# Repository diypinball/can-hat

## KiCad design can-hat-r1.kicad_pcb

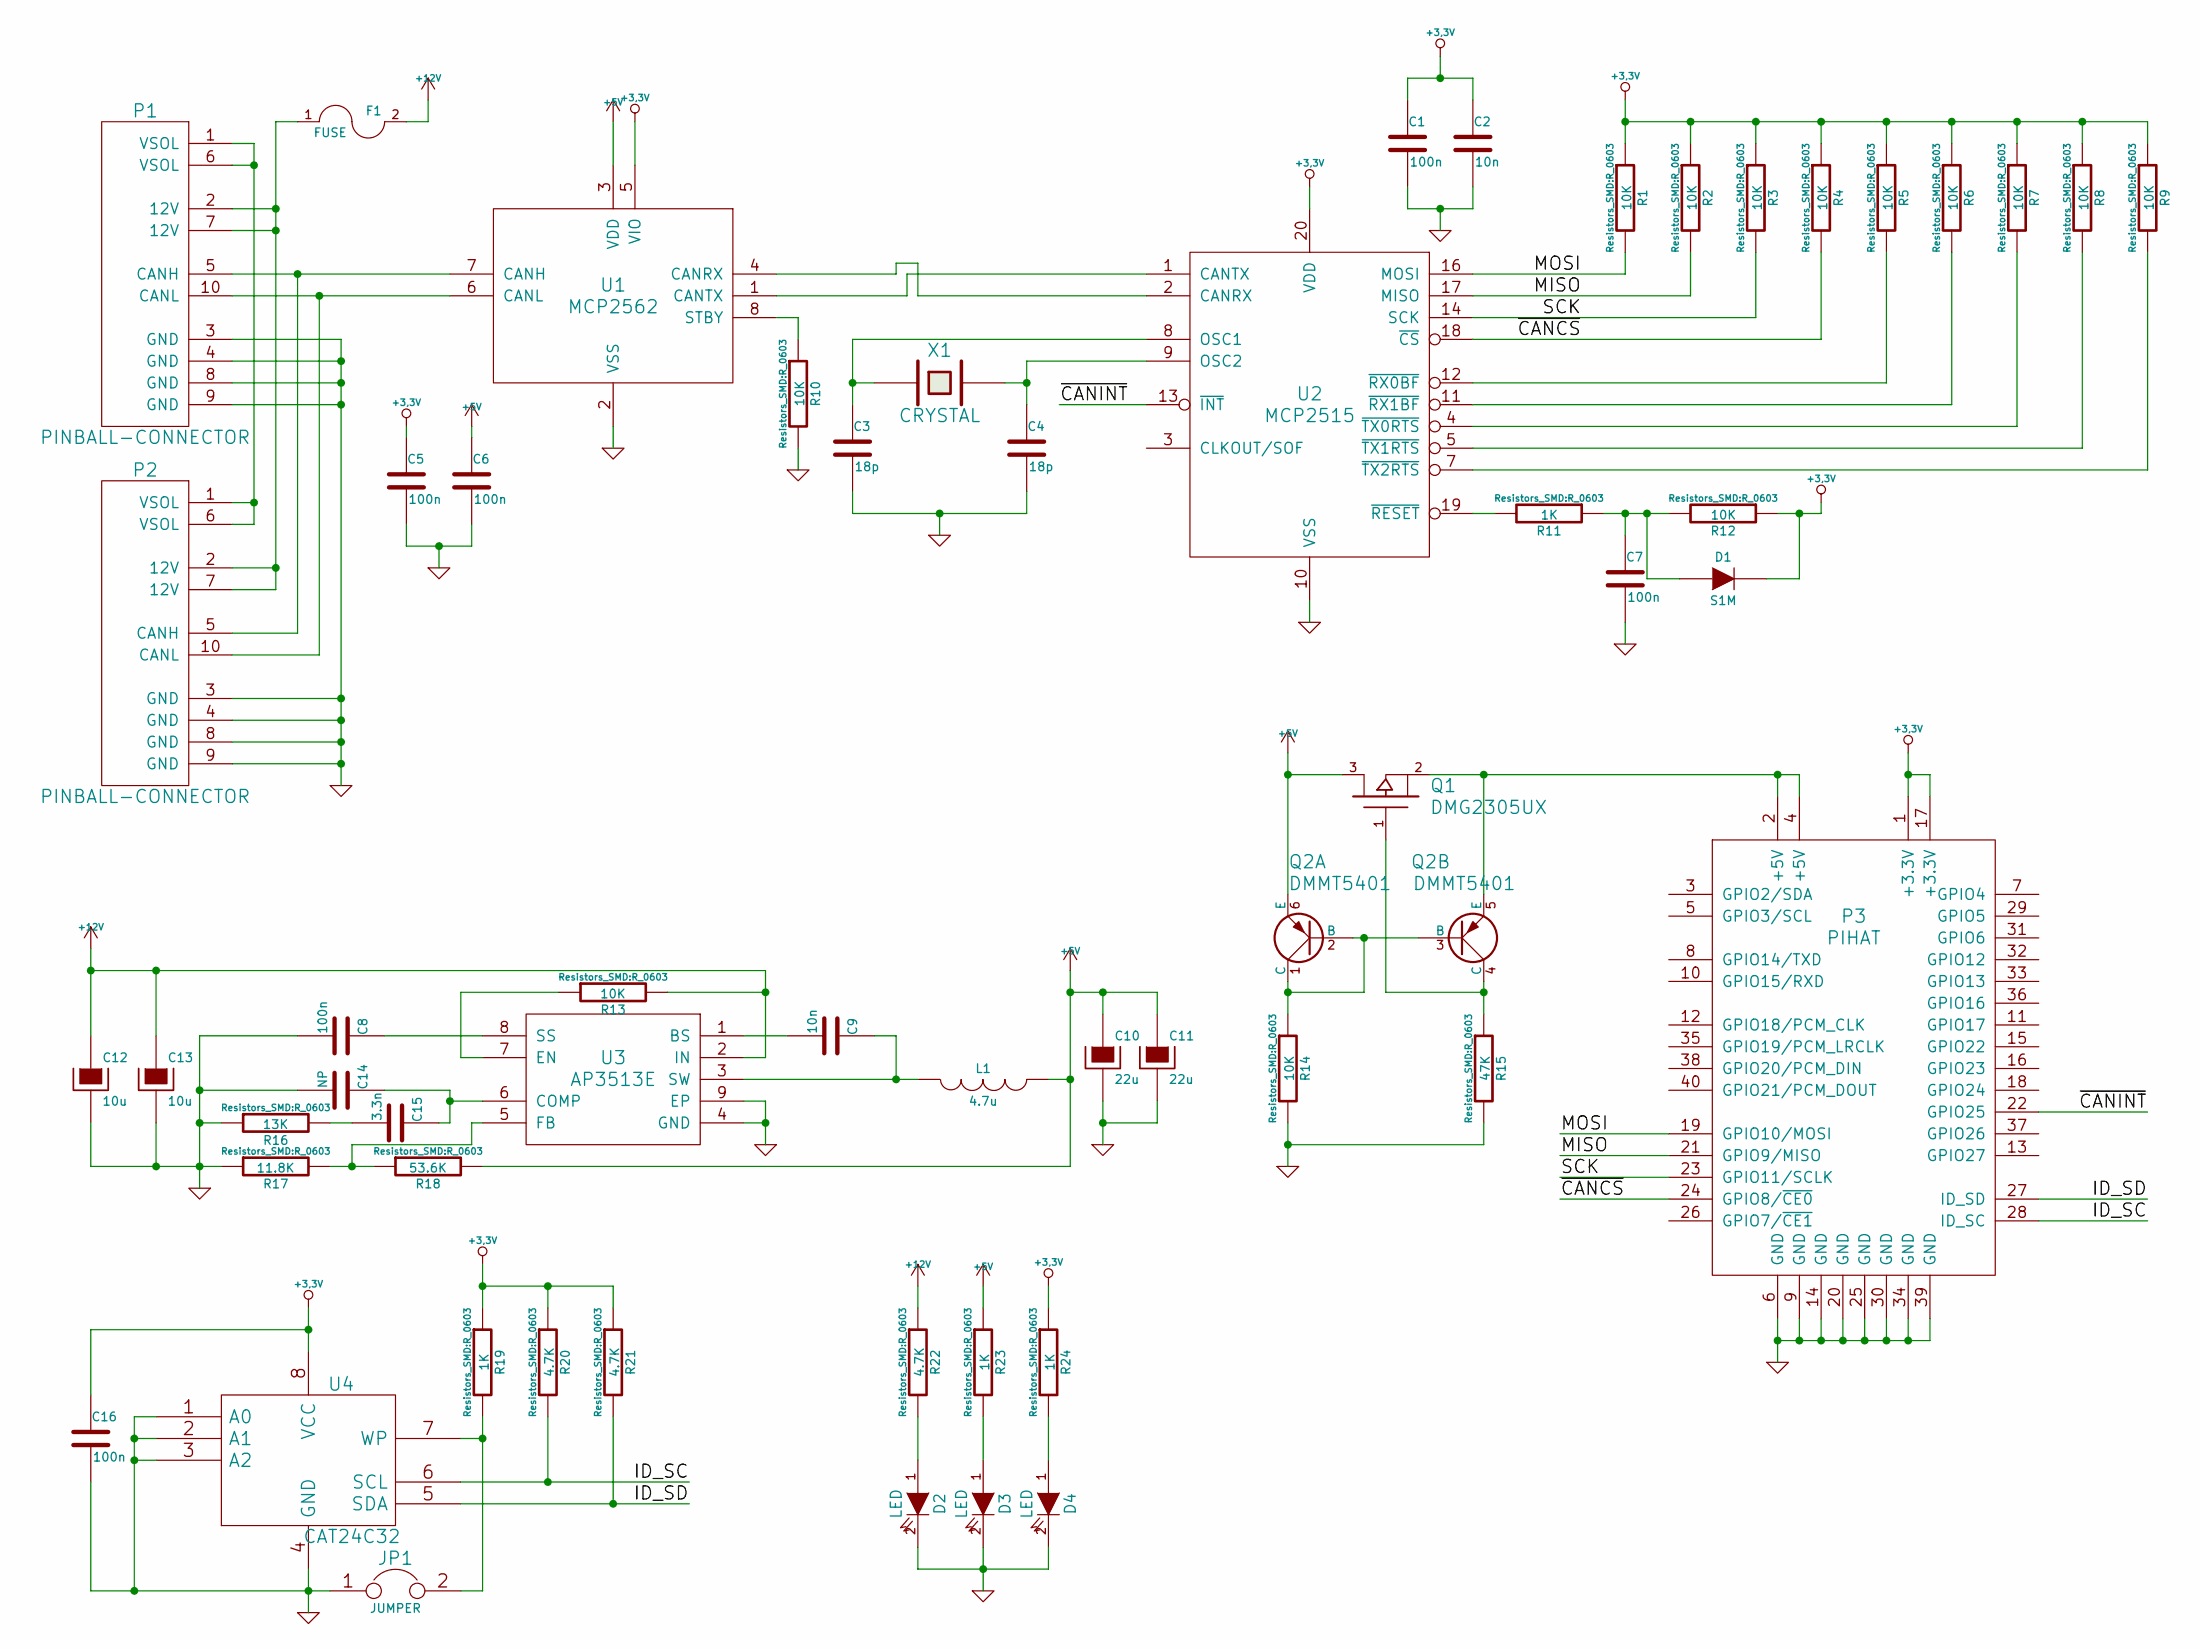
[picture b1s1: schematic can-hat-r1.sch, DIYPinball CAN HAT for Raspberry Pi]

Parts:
C1, C5, C6, C7, C8, C16: 100n; C_0603
C2, C9: 10n; C_0603
C3, C4: 18p; C_0603
C10, C11: 22u; c_elec_5x5.8
C12, C13: 10u; c_elec_5x5.8
C14: NP; C_0603
C15: 3.3n; C_0603
D1: S1M; Diode-SMA_Standard
D2, D3, D4: LED; LED-0603
F1: FUSE; FC203-20MM
JP1: JUMPER; S_JUMPER_2
L1: 4.7u; SELF-WE-PD-XXL
P1, P2: PINBALL-CONNECTOR; PINBALL-CONNECTOR-V
P3: PIHAT
Q1: DMG2305UX; SOT23
Q2: DMMT5401; SOT-23-6
R1, R2, R3, R4, R5, R6, R7, R8, R9, R10, R12, R13, R14: 10K; R_0603
R11, R19, R23, R24: 1K; R_0603
R15: 47K; R_0603
R16: 13K; R_0603
R17: 11.8K; R_0603
R18: 53.6K; R_0603
R20, R21, R22: 4.7K; R_0603
U1: MCP2562; SOIC-8_3.9x4.9mm_Pitch1.27mm
U2: MCP2515; SSOP-20_4.4x6.5mm_Pitch0.65mm
U3: AP3513E; SOIC-8-1EP_3.9x4.9mm_Pitch1.27mm
U4: CAT24C32; SOIC-8_3.9x4.9mm_Pitch1.27mm
X1: CRYSTAL; Q_49U3HMS

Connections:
+3.3V: C1.1, C2.1, C5.1, C16.1, D1.2 (K), P3.1 (+3.3V), P3.17 (+3.3V), R1.1, R2.1, R3.1, R4.1, R5.1, R6.1, R7.1, R8.1, R9.1, R12.1, R19.1, R20.1, R21.1, R24.1, U1.5 (VIO), U2.20 (VDD), U4.8 (VCC)
+5V: C6.1, C10.1, C11.1, L1.2, Q1.3 (D), Q2.6 (E), R18.2, R23.1, U1.3 (VDD)
+12V: C12.1, C13.1, F1.2, R13.2, R22.1, U3.2 (IN)
/ID_SC: P3.28 (ID_SC), R20.2, U4.6 (SCL)
/ID_SD: P3.27 (ID_SD), R21.2, U4.5 (SDA)
/MISO: P3.21 (GPIO9/MISO), R2.2, U2.17 (MISO)
/MOSI: P3.19 (GPIO10/MOSI), R1.2, U2.16 (MOSI)
/SCK: P3.23 (GPIO11/SCLK), R3.2, U2.14 (SCK)
/~CANCS: P3.24 (GPIO8/~CE0), R4.2, U2.18 (~CS)
/~CANINT: P3.22 (GPIO25), U2.13 (~INT)
GND: C1.2, C2.2, C3.2, C4.2, C5.2, C6.2, C7.2, C8.2, C10.2, C11.2, C12.2, C13.2, C14.2, C16.2, D2.2 (K), D3.2 (K), D4.2 (K), JP1.1, P1.3 (GND), P1.4 (GND), P1.8 (GND), P1.9 (GND), P2.3 (GND), P2.4 (GND), P2.8 (GND), P2.9 (GND), P3.6 (GND), P3.9 (GND), P3.14 (GND), P3.20 (GND), P3.25 (GND), P3.30 (GND), P3.34 (GND), P3.39 (GND), R10.2, R14.2, R15.2, R16.1, R17.1, U1.2 (VSS), U2.10 (VSS), U3.4 (GND), U3.9 (EP), U4.1 (A0), U4.2 (A1), U4.3 (A2), U4.4 (GND)
unnamed: C3.1, U2.8 (OSC1), X1.1
unnamed: C4.1, U2.9 (OSC2), X1.2
unnamed: C7.1, D1.1 (A), R11.1, R12.2
unnamed: C8.1, U3.8 (SS)
unnamed: C9.1, L1.1, U3.3 (SW)
unnamed: C9.2, U3.1 (BS)
unnamed: C14.1, C15.1, U3.6 (COMP)
unnamed: C15.2, R16.2
unnamed: D2.1 (A), R22.2
unnamed: D3.1 (A), R23.2
unnamed: D4.1 (A), R24.2
unnamed: F1.1, P1.2 (12V), P1.7 (12V), P2.2 (12V), P2.7 (12V)
unnamed: JP1.2, R19.2, U4.7 (WP)
unnamed: P1.1 (VSOL), P1.6 (VSOL), P2.1 (VSOL), P2.6 (VSOL)
unnamed: P1.5 (CANH), P2.5 (CANH), U1.7 (CANH)
unnamed: P1.10 (CANL), P2.10 (CANL), U1.6 (CANL)
unnamed: P3.2 (+5V), P3.4 (+5V), Q1.2 (S), Q2.5 (E)
unnamed: Q1.1 (G), Q2.4 (C), R15.1
unnamed: Q2.1 (C), Q2.2 (B), Q2.3 (B), R14.1
unnamed: R5.2, U2.12 (~RX0BF)
unnamed: R6.2, U2.11 (~RX1BF)
unnamed: R7.2, U2.4 (~TX0RTS)
unnamed: R8.2, U2.5 (~TX1RTS)
unnamed: R9.2, U2.7 (~TX2RTS)
unnamed: R10.1, U1.8 (STBY)
unnamed: R11.2, U2.19 (~RESET)
unnamed: R13.1, U3.7 (EN)
unnamed: R17.2, R18.1, U3.5 (FB)
unnamed: U1.1 (CANTX), U2.1 (CANTX)
unnamed: U1.4 (CANRX), U2.2 (CANRX)

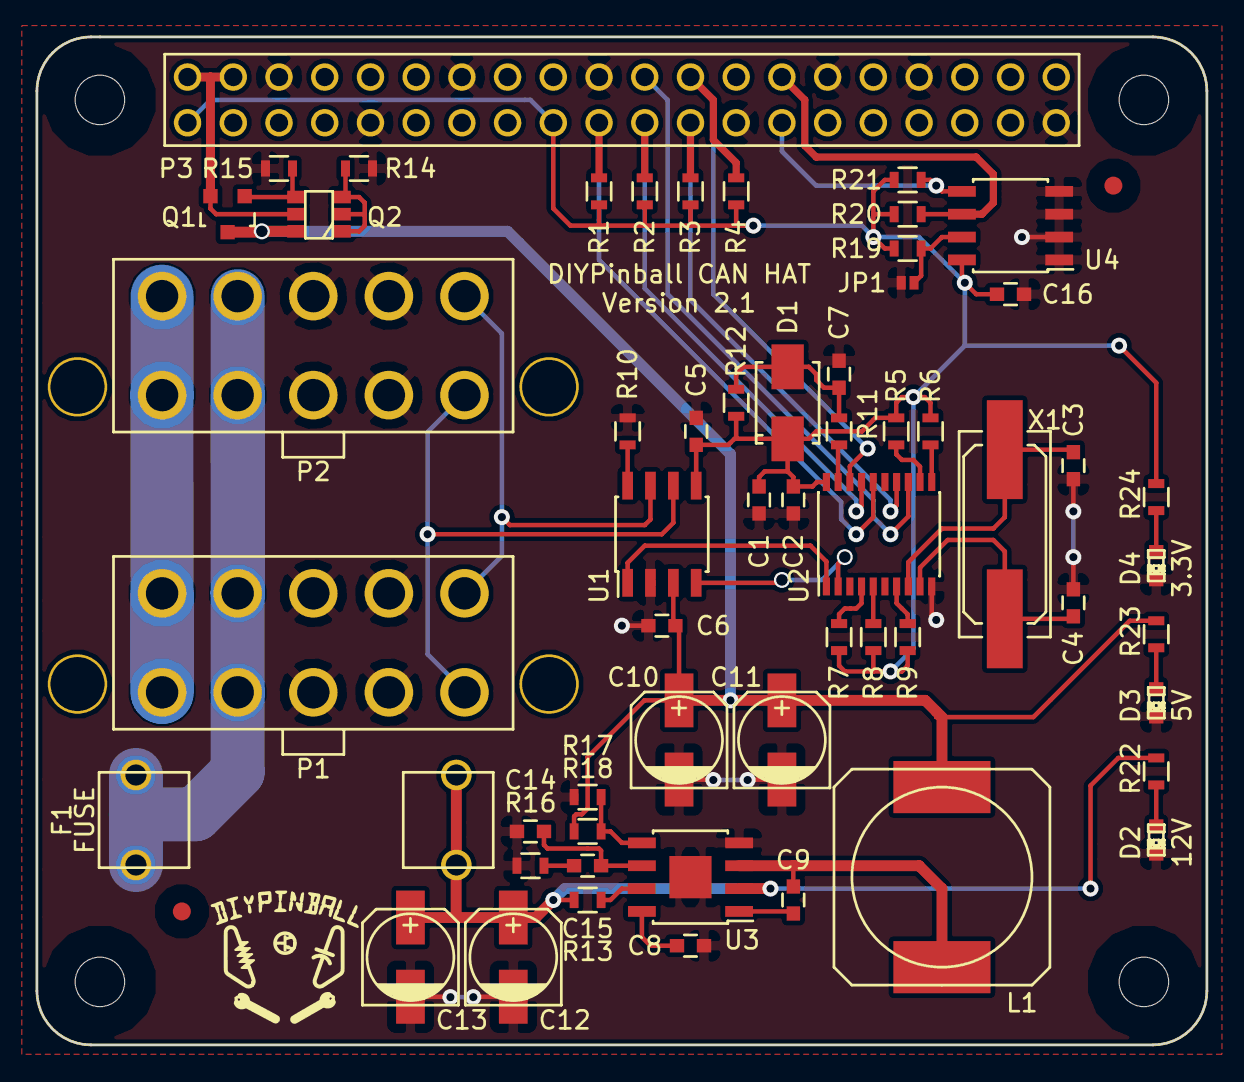
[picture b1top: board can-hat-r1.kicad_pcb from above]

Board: 2 copper layers, 65.0 x 56.0 mm, 59 parts (0 on the bottom side), 41 nets.

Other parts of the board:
FIDUCIAL: VAL**; FIDUCIAL
FIDUCIAL#2: VAL**; FIDUCIAL

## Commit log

2015-06-07 Adding gitignore
2015-06-07 Adding work done to date
2015-06-07 Removing useless drill diagrams
2015-06-08 Updating to correct wrong board dimensions (was 1mm too short) and to fix copper around screw holes (there shouldn't be any).
2015-11-11 Updated to latest version of KiCAD. Added PDF of schematic.
2016-09-09 Some minor updates
